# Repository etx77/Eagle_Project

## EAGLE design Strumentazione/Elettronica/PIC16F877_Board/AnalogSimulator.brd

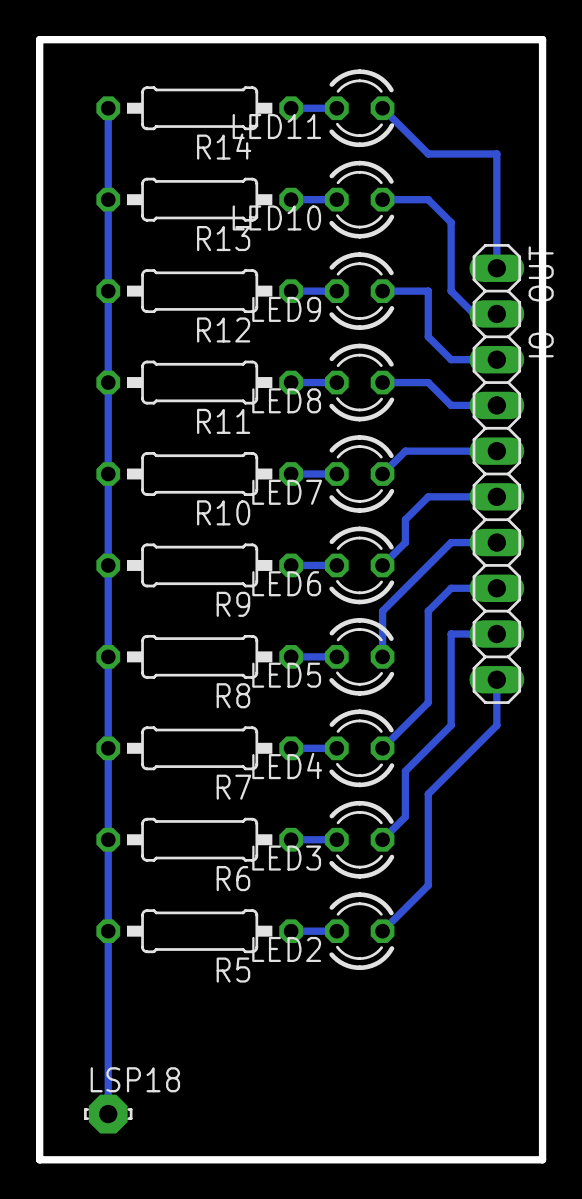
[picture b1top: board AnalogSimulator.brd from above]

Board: 2 copper layers, 27.9 x 62.2 mm, 22 parts (0 on the bottom side), 21 nets.

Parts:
IO-OUT: 1X10
LED2, LED3, LED4, LED5, LED6, LED7, LED8, LED9, LED10, LED11: LED3MM
LSP18: LSP10
R5, R6, R7, R8, R9, R10, R11, R12, R13, R14: 220; 0207/10

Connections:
unnamed: LED2.K, R5.1
unnamed: LED3.K, R6.1
unnamed: LED4.K, R7.1
unnamed: LED5.K, R8.1
unnamed: LED6.K, R9.1
unnamed: LED7.K, R10.1
unnamed: LED8.K, R11.1
unnamed: LED9.K, R12.1
unnamed: LED10.K, R13.1
unnamed: LED11.K, R14.1
unnamed: IO-OUT.10, LED2.A
unnamed: IO-OUT.9, LED3.A
unnamed: IO-OUT.8, LED4.A
unnamed: IO-OUT.7, LED5.A
unnamed: IO-OUT.6, LED6.A
unnamed: IO-OUT.5, LED7.A
unnamed: IO-OUT.4, LED8.A
unnamed: IO-OUT.3, LED9.A
unnamed: IO-OUT.2, LED10.A
unnamed: IO-OUT.1, LED11.A
unnamed: LSP18.MP, R5.2, R6.2, R7.2, R8.2, R9.2, R10.2, R11.2, R12.2, R13.2, R14.2

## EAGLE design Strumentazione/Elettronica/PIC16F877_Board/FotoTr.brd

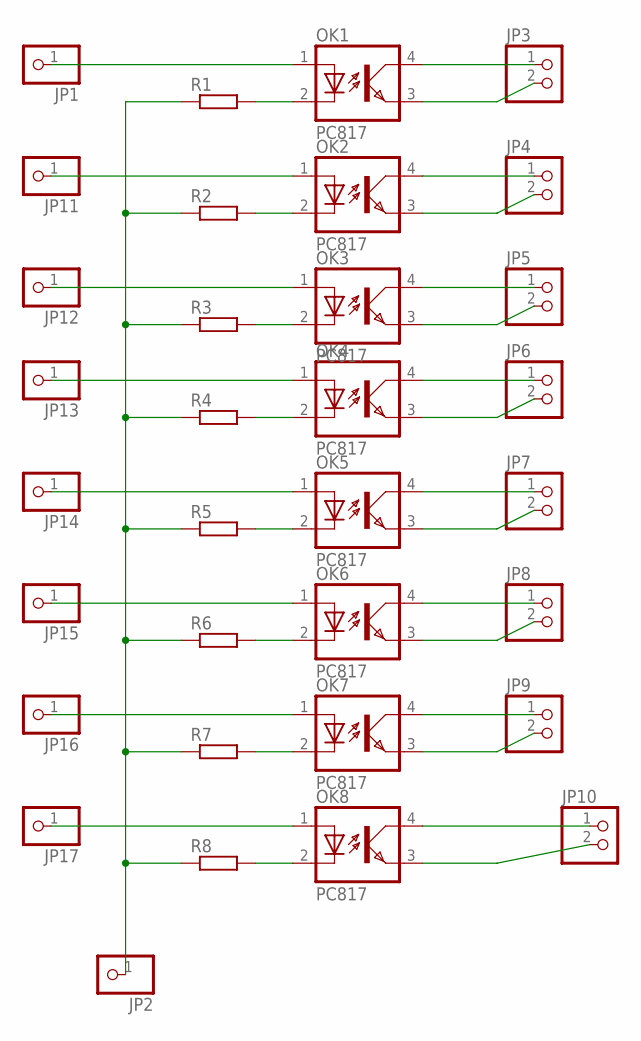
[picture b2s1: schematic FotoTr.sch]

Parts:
JP1, JP2, JP11, JP12, JP13, JP14, JP15, JP16, JP17: PINHD-1X1; 1X01
JP3, JP4, JP5, JP6, JP7, JP8, JP9, JP10: PINHD-1X2; 1X02
OK1, OK2, OK3, OK4, OK5, OK6, OK7, OK8: PC817; DIL04
R1, R2, R3, R4, R5, R6, R7, R8: R-EU_0204/2V; 0204V

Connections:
unnamed: OK1.2 (C), R1.2
unnamed: OK2.2 (C), R2.2
unnamed: OK3.2 (C), R3.2
unnamed: OK4.2 (C), R4.2
unnamed: OK5.2 (C), R5.2
unnamed: OK6.2 (C), R6.2
unnamed: OK7.2 (C), R7.2
unnamed: OK8.2 (C), R8.2
unnamed: JP2.1, R1.1, R2.1, R3.1, R4.1, R5.1, R6.1, R7.1, R8.1
unnamed: JP1.1, OK1.1 (A)
unnamed: JP11.1, OK2.1 (A)
unnamed: JP12.1, OK3.1 (A)
unnamed: JP13.1, OK4.1 (A)
unnamed: JP14.1, OK5.1 (A)
unnamed: JP15.1, OK6.1 (A)
unnamed: JP16.1, OK7.1 (A)
unnamed: JP17.1, OK8.1 (A)
unnamed: JP3.1, OK1.4 (COL)
unnamed: JP3.2, OK1.3 (EMIT)
unnamed: JP4.1, OK2.4 (COL)
unnamed: JP4.2, OK2.3 (EMIT)
unnamed: JP5.1, OK3.4 (COL)
unnamed: JP5.2, OK3.3 (EMIT)
unnamed: JP6.1, OK4.4 (COL)
unnamed: JP6.2, OK4.3 (EMIT)
unnamed: JP7.1, OK5.4 (COL)
unnamed: JP7.2, OK5.3 (EMIT)
unnamed: JP8.1, OK6.4 (COL)
unnamed: JP8.2, OK6.3 (EMIT)
unnamed: JP9.1, OK7.4 (COL)
unnamed: JP9.2, OK7.3 (EMIT)
unnamed: JP10.1, OK8.4 (COL)
unnamed: JP10.2, OK8.3 (EMIT)

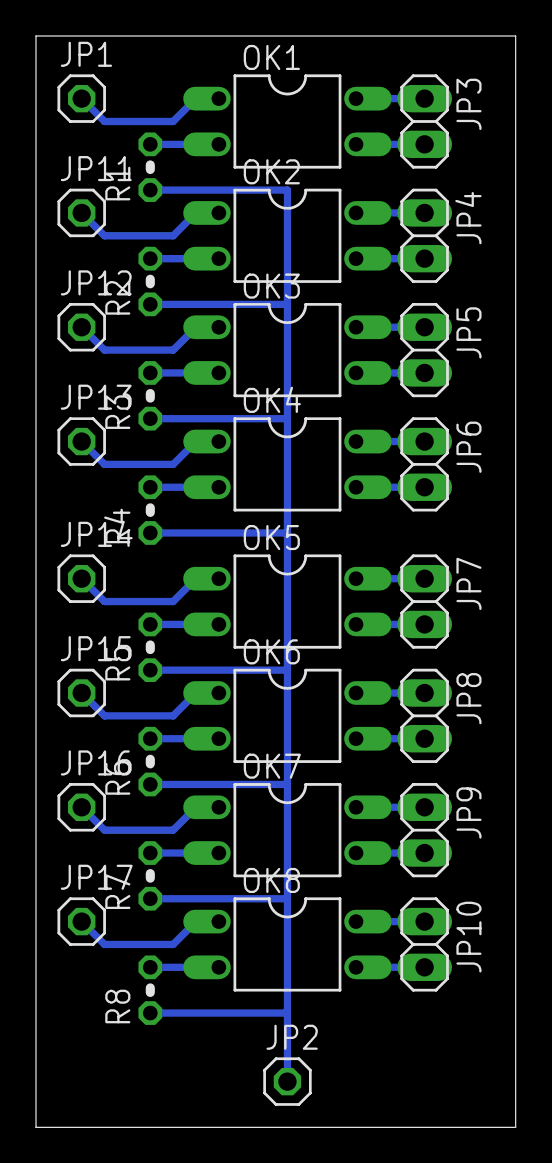
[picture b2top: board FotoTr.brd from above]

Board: 2 copper layers, 26.6 x 60.6 mm, 33 parts (0 on the bottom side), 33 nets.

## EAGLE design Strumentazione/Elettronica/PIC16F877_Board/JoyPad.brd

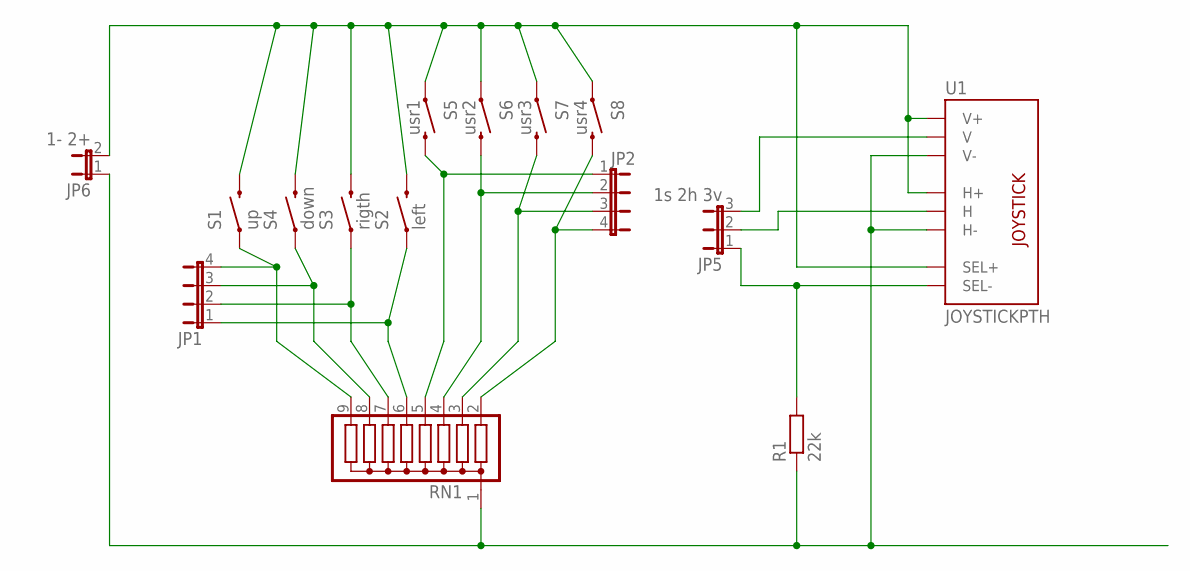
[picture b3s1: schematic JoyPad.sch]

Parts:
JP1, JP2: JP4E; JP4
JP5: 1s 2h 3v; JP2
JP6: 1- 2+; JP1
R1: 22k; 0207/15
RN1: G08R; SIL9
S1: up; TACTILE-PTH
S2: left; TACTILE-PTH
S3: rigth; TACTILE-PTH
S4: down; TACTILE-PTH
S5: usr1; TACTILE-PTH
S6: usr2; TACTILE-PTH
S7: usr3; TACTILE-PTH
S8: usr4; TACTILE-PTH
U1: JOYSTICKPTH; JOYSTICK

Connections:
unnamed: JP6.1, R1.1, RN1.1, U1.H3 (H-), U1.V3 (V-)
unnamed: JP1.4, RN1.9, S1.1
unnamed: JP1.3, RN1.8, S4.1
unnamed: JP1.2, RN1.7, S3.1
unnamed: JP1.1, RN1.6, S2.1
unnamed: JP2.1, RN1.5, S5.3 (2)
unnamed: JP2.2, RN1.4, S6.3 (2)
unnamed: JP2.3, RN1.3, S7.3 (2)
unnamed: JP2.4, RN1.2, S8.3 (2)
unnamed: JP6.2, S1.3 (2), S2.3 (2), S3.3 (2), S4.3 (2), S5.1, S6.1, S7.1, S8.1, U1.B1A (SEL+), U1.H1 (H+), U1.V1 (V+)
unnamed: JP5.1, R1.2, U1.B2A (SEL-)
unnamed: JP5.3, U1.V2 (V)
unnamed: JP5.2, U1.H2 (H)

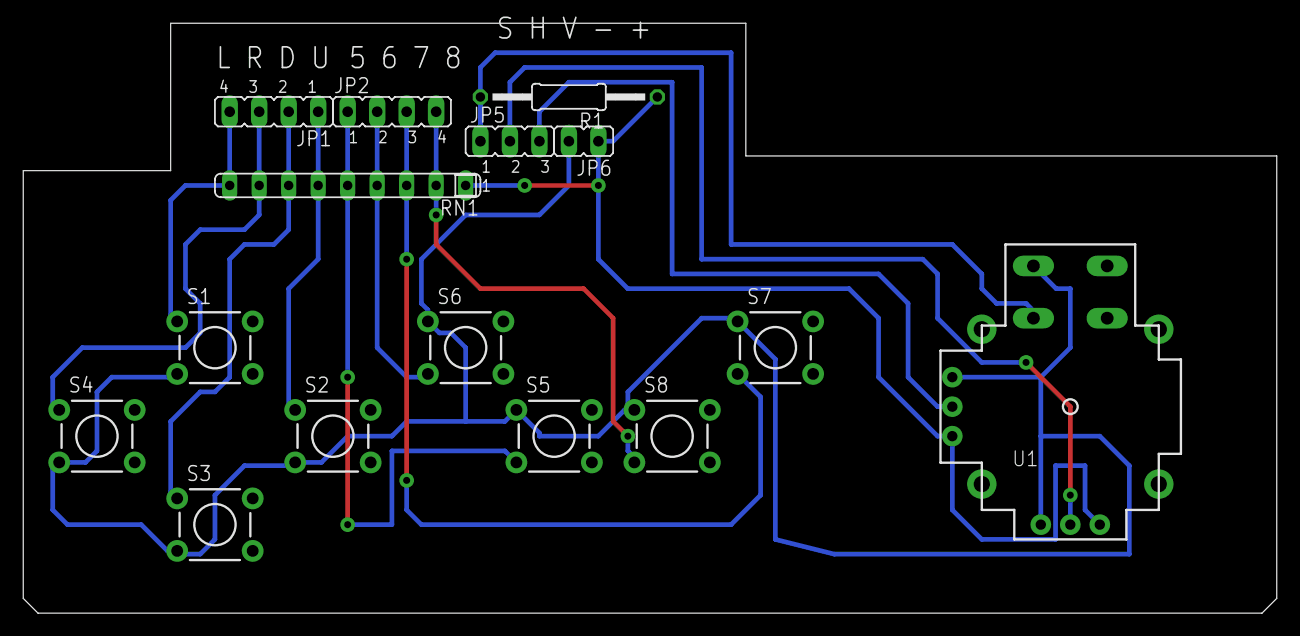
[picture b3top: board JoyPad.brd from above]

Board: 2 copper layers, 108.0 x 50.8 mm, 15 parts (0 on the bottom side), 13 nets.

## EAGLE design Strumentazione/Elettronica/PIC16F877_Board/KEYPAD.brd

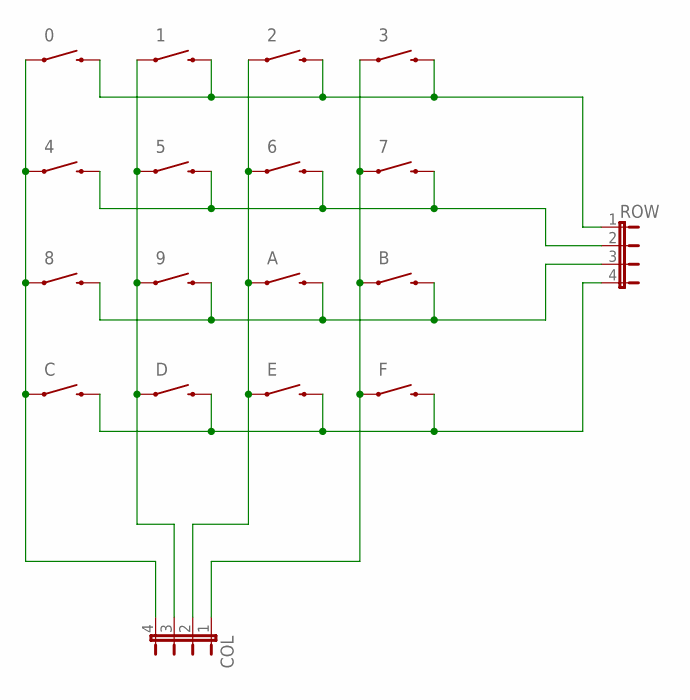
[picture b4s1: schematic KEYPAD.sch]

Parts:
0, 1, 2, 3, 4, 5, 6, 7, 8, 9: SWITCH-MOMENTARY-2PTH; TACTILE-PTH
A: SWITCH-MOMENTARY-2PTH; TACTILE-PTH
B: SWITCH-MOMENTARY-2PTH; TACTILE-PTH
C: SWITCH-MOMENTARY-2PTH; TACTILE-PTH
COL: JP4E; JP4
D: SWITCH-MOMENTARY-2PTH; TACTILE-PTH
E: SWITCH-MOMENTARY-2PTH; TACTILE-PTH
F: SWITCH-MOMENTARY-2PTH; TACTILE-PTH
ROW: JP4E; JP4

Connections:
unnamed: 0.1, 4.1, 8.1, C.1, COL.4
unnamed: 1.1, 5.1, 9.1, COL.3, D.1
unnamed: 2.1, 6.1, A.1, COL.2, E.1
unnamed: 3.1, 7.1, B.1, COL.1, F.1
unnamed: 0.3 (2), 1.3 (2), 2.3 (2), 3.3 (2), ROW.1
unnamed: 8.3 (2), 9.3 (2), A.3 (2), B.3 (2), ROW.3
unnamed: C.3 (2), D.3 (2), E.3 (2), F.3 (2), ROW.4
unnamed: 4.3 (2), 5.3 (2), 6.3 (2), 7.3 (2), ROW.2

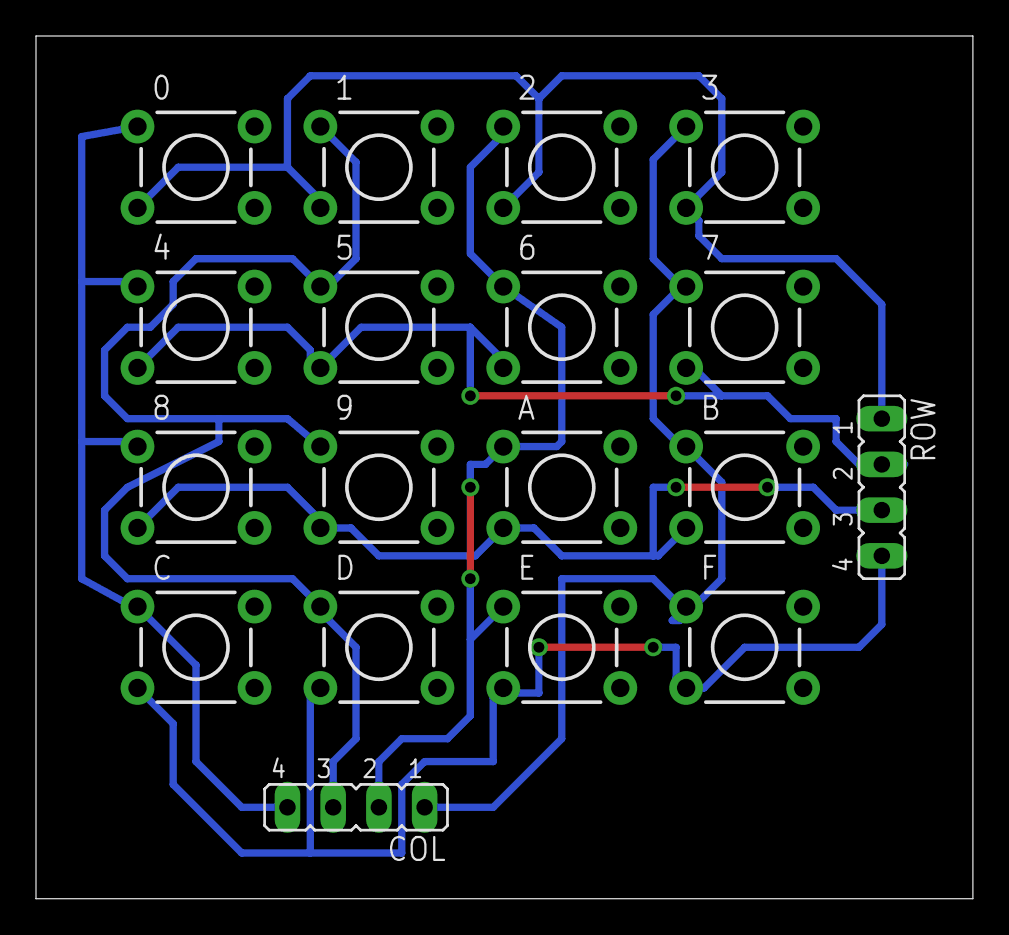
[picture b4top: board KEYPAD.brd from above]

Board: 2 copper layers, 52.0 x 47.9 mm, 18 parts (0 on the bottom side), 8 nets.

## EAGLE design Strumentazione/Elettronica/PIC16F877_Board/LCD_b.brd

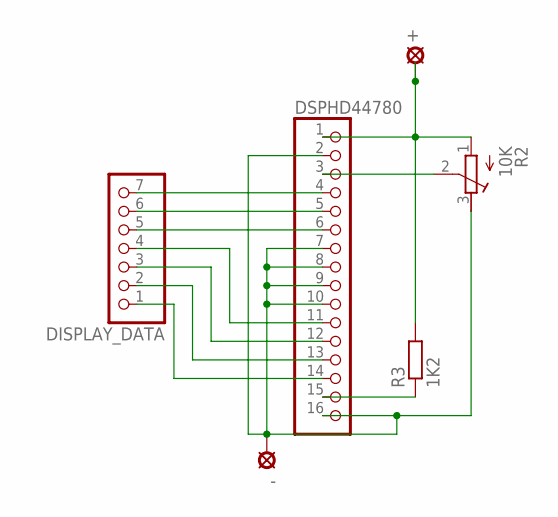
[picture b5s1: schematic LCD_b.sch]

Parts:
+: LSP10
-: LSP10
DISPLAY_DATA: PINHD-1X7; 1X07
DSPHD44780: PINHD-1X16; 1X16
R2: 10K; RTRIM3339P
R3: 1K2; 0207/10

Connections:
unnamed: -.MP, DSPHD44780.2, DSPHD44780.7, DSPHD44780.8, DSPHD44780.9, DSPHD44780.10, DSPHD44780.16, R2.3 (E)
unnamed: DISPLAY_DATA.5, DSPHD44780.6
unnamed: DISPLAY_DATA.6, DSPHD44780.5
unnamed: DSPHD44780.15, R3.1
unnamed: DISPLAY_DATA.1, DSPHD44780.14
unnamed: DISPLAY_DATA.2, DSPHD44780.13
unnamed: DISPLAY_DATA.3, DSPHD44780.12
unnamed: DISPLAY_DATA.4, DSPHD44780.11
unnamed: DISPLAY_DATA.7, DSPHD44780.4
unnamed: DSPHD44780.3, R2.2 (S)
unnamed: +.MP, DSPHD44780.1, R2.1 (A), R3.2

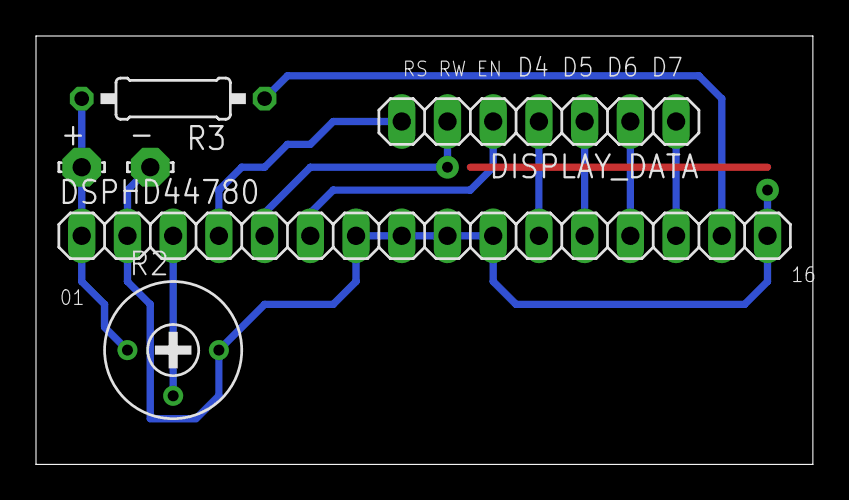
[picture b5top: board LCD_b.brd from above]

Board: 2 copper layers, 43.2 x 23.8 mm, 6 parts (0 on the bottom side), 11 nets.

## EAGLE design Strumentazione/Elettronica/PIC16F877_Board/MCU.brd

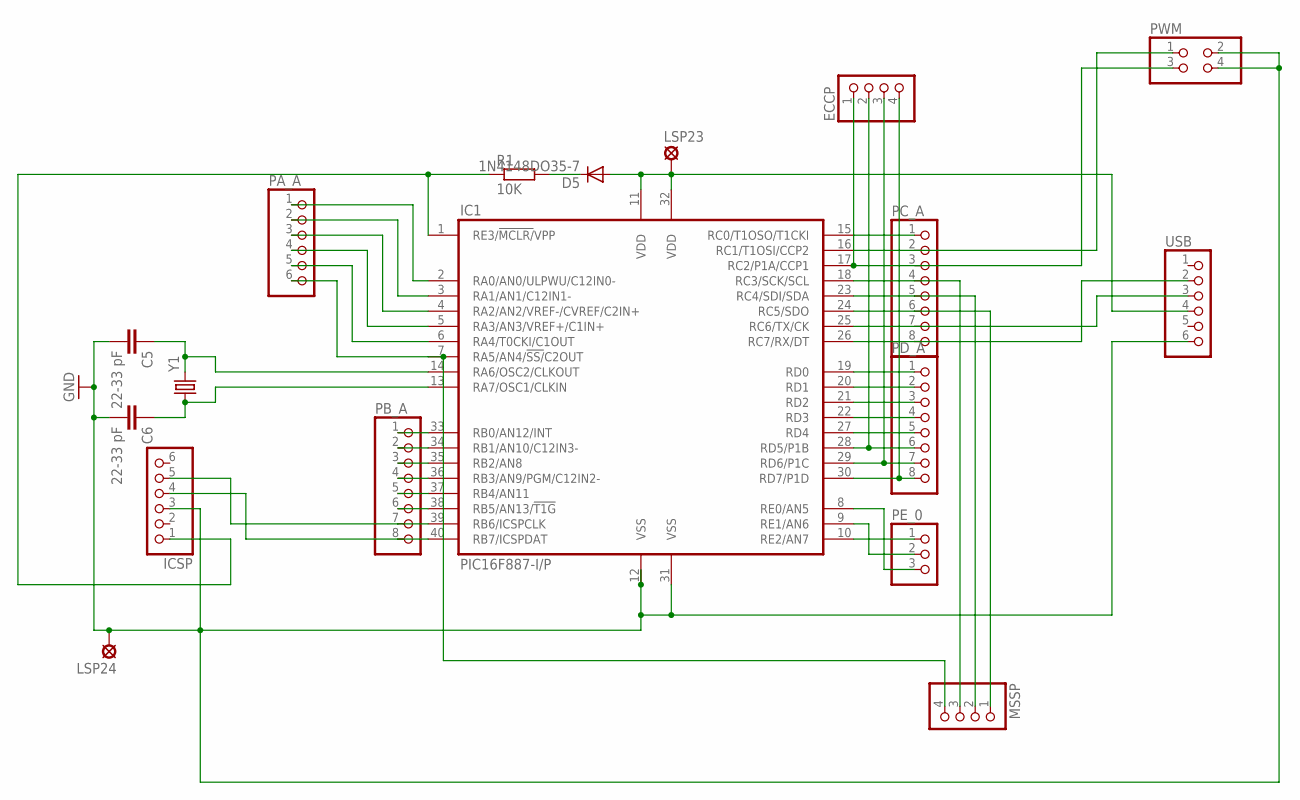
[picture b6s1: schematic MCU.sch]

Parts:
C5, C6: 22-33 pF; C025-024X044
D5: 1N4148DO35-7; DO35-7
ECCP: PINHD-1X4; 1X04
IC1: PIC16F887-I/P; DIL40
ICSP: PINHD-1X6; 1X06
LSP23, LSP24: LSP10
MSSP: PINHD-1X4; 1X04
PA_A: PINHD-1X6; 1X06
PB_A: PINHD-1X8; 1X08
PC_A: PINHD-1X8; 1X08
PD_A: PINHD-1X8; 1X08
PE_0: PINHD-1X3; 1X03
PWM: PINHD-2X2; 2X02
R1: 10K; 0207/10
USB: PINHD-1X6; 1X06
Y1: CRYSTALHC49UV; HC49U-V

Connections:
GND: C5.2, C6.2, IC1.12 (VSS), IC1.31 (VSS), ICSP.3, LSP24.MP, PWM.2, PWM.4, USB.6
unnamed: C5.1, IC1.14 (RA6/OSC2/CLKOUT), Y1.2
unnamed: IC1.15 (RC0/T1OSO/T1CKI), PC_A.1
unnamed: IC1.33 (RB0/AN12/INT), PB_A.1
unnamed: IC1.34 (RB1/AN10/C12IN3-), PB_A.2
unnamed: IC1.35 (RB2/AN8), PB_A.3
unnamed: IC1.36 (RB3/AN9/PGM/C12IN2-), PB_A.4
unnamed: IC1.2 (RA0/AN0/ULPWU/C12IN0-), PA_A.1
unnamed: IC1.3 (RA1/AN1/C12IN1-), PA_A.2
unnamed: IC1.4 (RA2/AN2/VREF-/CVREF/C2IN+), PA_A.3
unnamed: IC1.5 (RA3/AN3/VREF+/C1IN+), PA_A.4
unnamed: IC1.6 (RA4/T0CKI/C1OUT), PA_A.5
unnamed: IC1.7 (RA5/AN4/!SS/!C2OUT), MSSP.4, PA_A.6
unnamed: IC1.1 (RE3/!MCLR/!VPP), ICSP.1, R1.1
unnamed: IC1.19 (RD0), PD_A.1
unnamed: IC1.37 (RB4/AN11), PB_A.5
unnamed: IC1.38 (RB5/AN13/!T1G), PB_A.6
unnamed: IC1.39 (RB6/ICSPCLK), ICSP.5, PB_A.7
unnamed: IC1.40 (RB7/ICSPDAT), ICSP.4, PB_A.8
unnamed: IC1.20 (RD1), PD_A.2
unnamed: IC1.16 (RC1/T1OSI/CCP2), PC_A.2, PWM.1
unnamed: C6.1, IC1.13 (RA7/OSC1/CLKIN), Y1.1
unnamed: IC1.18 (RC3/SCK/SCL), MSSP.3, PC_A.4
unnamed: IC1.23 (RC4/SDI/SDA), MSSP.2, PC_A.5
unnamed: IC1.24 (RC5/SDO), MSSP.1, PC_A.6
unnamed: IC1.25 (RC6/TX/CK), PC_A.7, USB.3
unnamed: IC1.26 (RC7/RX/DT), PC_A.8, USB.2
unnamed: IC1.21 (RD2), PD_A.3
unnamed: IC1.22 (RD3), PD_A.4
unnamed: IC1.27 (RD4), PD_A.5
unnamed: ECCP.2, IC1.28 (RD5/P1B), PD_A.6
unnamed: ECCP.3, IC1.29 (RD6/P1C), PD_A.7
unnamed: ECCP.4, IC1.30 (RD7/P1D), PD_A.8
unnamed: ECCP.1, IC1.17 (RC2/P1A/CCP1), PC_A.3, PWM.3
unnamed: IC1.9 (RE1/AN6), PE_0.2
unnamed: IC1.8 (RE0/AN5), PE_0.3
unnamed: IC1.10 (RE2/AN7), PE_0.1
unnamed: D5.C, R1.2
unnamed: D5.A, IC1.11 (VDD), IC1.32 (VDD), LSP23.MP, USB.4

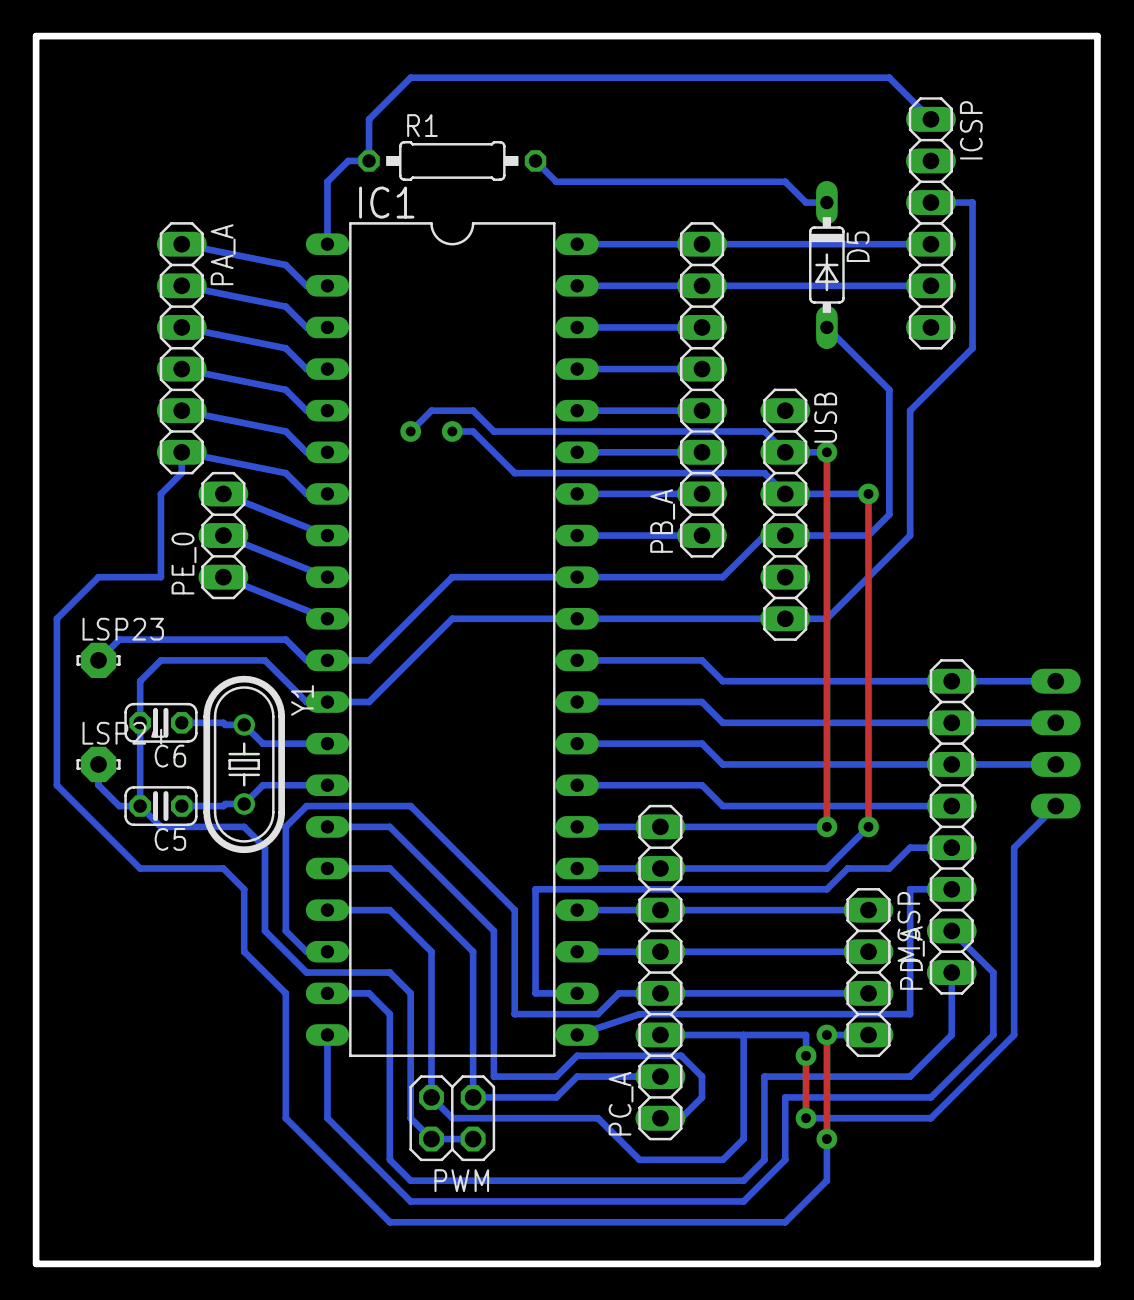
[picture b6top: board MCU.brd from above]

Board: 2 copper layers, 64.8 x 74.9 mm, 18 parts (1 on the bottom side), 39 nets.

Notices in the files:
parts and their libraries:
SparkFun-Electromechanical: Licensing: Creative Commons ShareAlike 4.0 International - https://creativecommons.org/licenses/by-sa/4.0
